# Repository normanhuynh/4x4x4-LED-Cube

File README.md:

# 4x4x4 LED Cube

This is a hand-soldered, reprogrammable 4x4x4 LED cube that uses Arduino - an open source IDE used to control user-made projects. This compact cube lights up with different patterns and is used to impress friends and family or as an amazing decoration for your desk. Of course, the hardware is not supplied in this repo - you will have to source that yourself.

# Main Components

  - ATmega328 microcontroller 
  - 2 x 74HC595N shift registers 
  - 4x4x4 cube matrix
  - 4 x BC327 transistors that control each layer of the cube.

Datasheets for the ATmega328 and for the 74HC595N are enclosed in the enclosed .zip file.

# How it Works - Quick Rundown
The LEDs are controlled by 2 shift registers that receive 16 bits from the programmed microcontroller. The shift registers then send out ON/OFF states to each layer of the cube’s cathodes before each corresponding layer anode is written to a LOW state in order to light the LEDs that were written to a LOW state. This process is rapidly repeated to give the impression that all LEDs in each layer are lit up simultaneously.

# Applications Used

  - **Arduino** - to create the LED cube sketch code
  - **Eagle** - to create the PCB and schematic

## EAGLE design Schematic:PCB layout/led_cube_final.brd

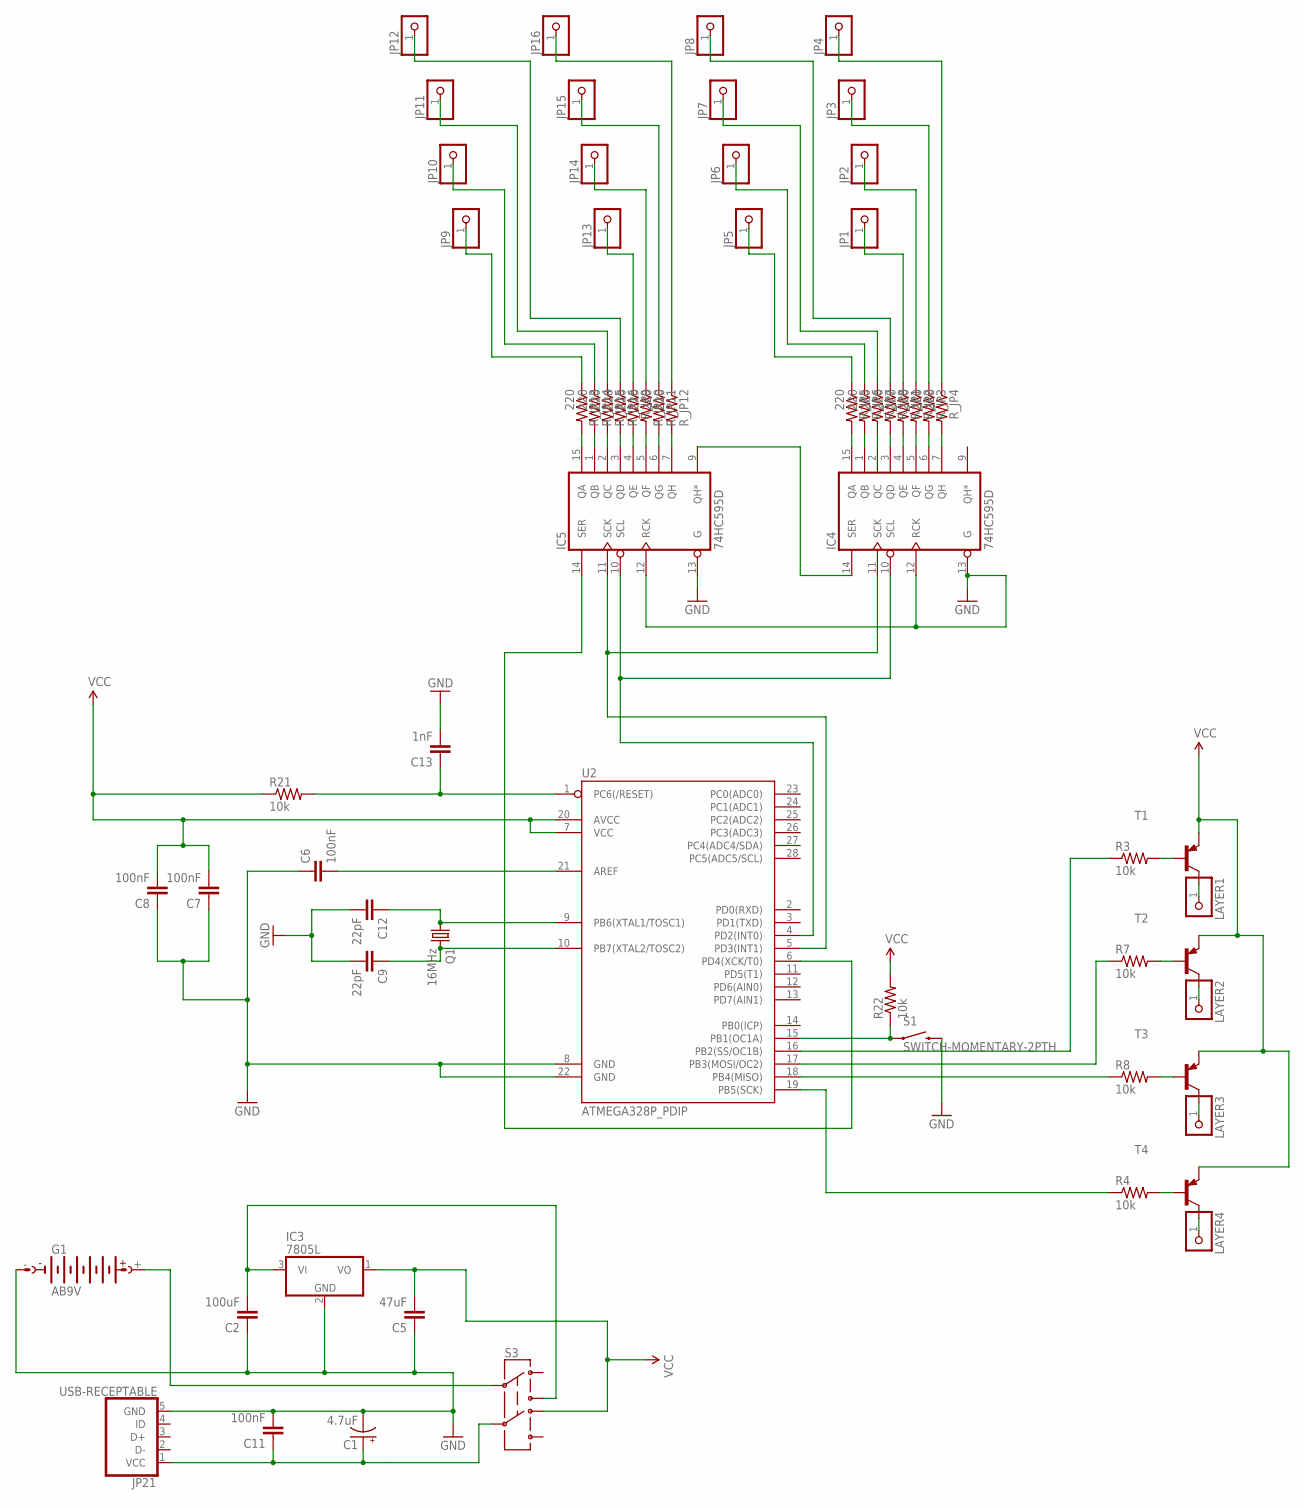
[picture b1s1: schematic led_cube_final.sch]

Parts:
C1: 4.7uF; E2-5
C2: 100uF; 0805
C5: 47uF; 0805
C6, C7, C8, C11: 100nF; 0805
C9, C12: 22pF; 0805
C13: 1nF; 0805
G1: AB9V
IC3: 7805L; TO92
IC4, IC5: 74HC595D; SO16
JP1, JP2, JP3, JP4, JP5, JP6, JP7, JP8, JP9, JP10, JP11, JP12, JP13, JP14, JP15, JP16: PINHD-1X1; 1X01
JP21: USB-RECEPTABLE; FCI-10103594-0001LF
LAYER1, LAYER2, LAYER3, LAYER4: PINHD-1X1; 1X01
Q1: 16MHz; HC49/S
R3, R4, R7, R8, R21, R22: 10k; 0805
R_JP1, R_JP2, R_JP3, R_JP4, R_JP5, R_JP6, R_JP7, R_JP8, R_JP9, R_JP10, R_JP11, R_JP12, R_JP13, R_JP14, R_JP15, R_JP16: 220; 0805
S1: SWITCH-MOMENTARY-2PTH; TACTILE-PTH
S3: SWITCH-DPDTOS; OS
T1, T2, T3, T4: BC327-16-PNP-TO92-EBC; TO92-EBC
U2: ATMEGA328P_PDIP; DIL28-3

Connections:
GND: C1.-, C2.1, C5.1, C6.1, C7.1, C8.1, C9.2, C11.2, C12.2, C13.2, G1.-, IC3.2 (GND), IC4.8 (GND), IC4.12 (RCK), IC4.13 (G), IC5.8 (GND), IC5.12 (RCK), IC5.13 (G), JP21.5 (GND), S1.3 (2), U2.8 (GND), U2.22 (GND)
unnamed: R4.2, T4.B
unnamed: R3.2, T1.B
unnamed: R7.2, T2.B
unnamed: IC4.10 (SCL), IC5.10 (SCL), U2.4 (PD2(INT0))
unnamed: JP1.1, R_JP1.1
unnamed: JP2.1, R_JP2.1
unnamed: R8.2, T3.B
unnamed: JP3.1, R_JP3.1
unnamed: JP4.1, R_JP4.1
unnamed: JP5.1, R_JP5.1
unnamed: JP6.1, R_JP6.1
unnamed: R22.1, S1.1, U2.15 (PB1(OC1A))
unnamed: LAYER3.1, T3.C
unnamed: R4.1, U2.19 (PB5(SCK))
unnamed: JP7.1, R_JP7.1
unnamed: JP8.1, R_JP8.1
unnamed: JP13.1, R_JP9.1
unnamed: JP14.1, R_JP10.1
unnamed: JP15.1, R_JP11.1
unnamed: JP16.1, R_JP12.1
unnamed: JP9.1, R_JP13.1
unnamed: JP10.1, R_JP14.1
unnamed: JP11.1, R_JP15.1
unnamed: JP12.1, R_JP16.1
unnamed: IC4.7 (QH), R_JP4.2
unnamed: IC4.6 (QG), R_JP3.2
unnamed: IC4.5 (QF), R_JP2.2
unnamed: IC4.4 (QE), R_JP1.2
unnamed: IC4.3 (QD), R_JP8.2
unnamed: IC4.2 (QC), R_JP7.2
unnamed: IC4.1 (QB), R_JP6.2
unnamed: IC4.15 (QA), R_JP5.2
unnamed: IC5.7 (QH), R_JP12.2
unnamed: IC5.6 (QG), R_JP11.2
unnamed: IC5.5 (QF), R_JP10.2
unnamed: IC5.4 (QE), R_JP9.2
unnamed: IC5.3 (QD), R_JP16.2
unnamed: IC5.2 (QC), R_JP15.2
unnamed: IC5.1 (QB), R_JP14.2
unnamed: IC5.15 (QA), R_JP13.2
unnamed: IC4.14 (SER), IC5.9 (QH*)
unnamed: LAYER4.1, T4.C
unnamed: R8.1, U2.18 (PB4(MISO))
unnamed: IC4.11 (SCK), IC5.11 (SCK), U2.5 (PD3(INT1))
unnamed: C2.2, IC3.3 (VI), S3.3
unnamed: C9.1, Q1.2, U2.10 (PB7(XTAL2/TOSC2))
unnamed: IC5.14 (SER), U2.6 (PD4(XCK/T0))
unnamed: R7.1, U2.17 (PB3(MOSI/OC2))
unnamed: C12.1, Q1.1, U2.9 (PB6(XTAL1/TOSC1))
unnamed: LAYER2.1, T2.C
unnamed: LAYER1.1, T1.C
unnamed: R3.1, U2.16 (PB2(SS/OC1B))
unnamed: C13.1, R21.2, U2.1 (PC6(/RESET))
unnamed: C6.2, U2.21 (AREF)
unnamed: G1.+, S3.2
unnamed: C1.+, C11.1, JP21.1 (VCC), S3.5
VCC: C5.2, C7.2, C8.2, IC3.1 (VO), IC4.16 (VCC), IC5.16 (VCC), R21.1, R22.2, S3.4, T1.E, T2.E, T3.E, T4.E, U2.7 (VCC), U2.20 (AVCC)

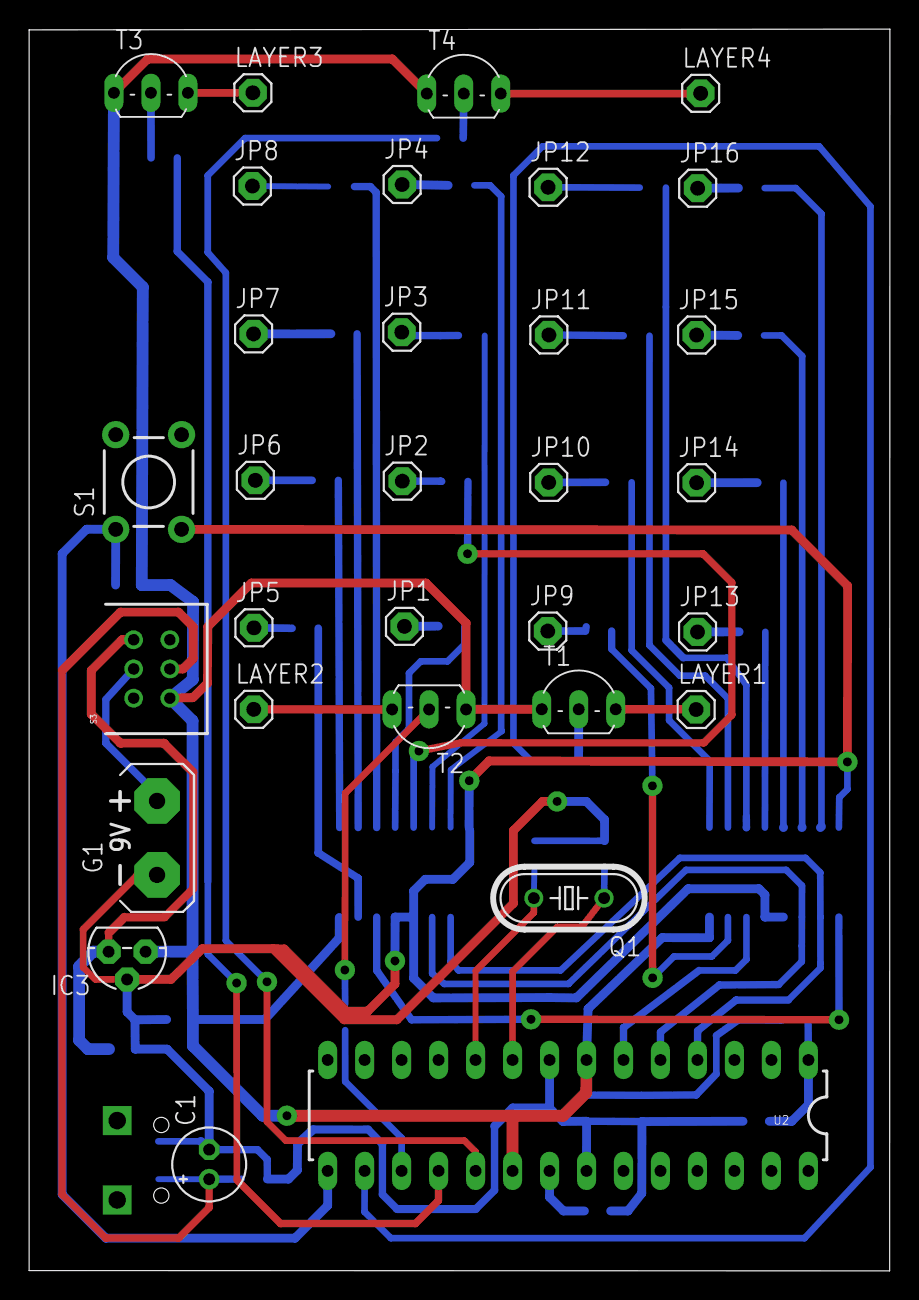
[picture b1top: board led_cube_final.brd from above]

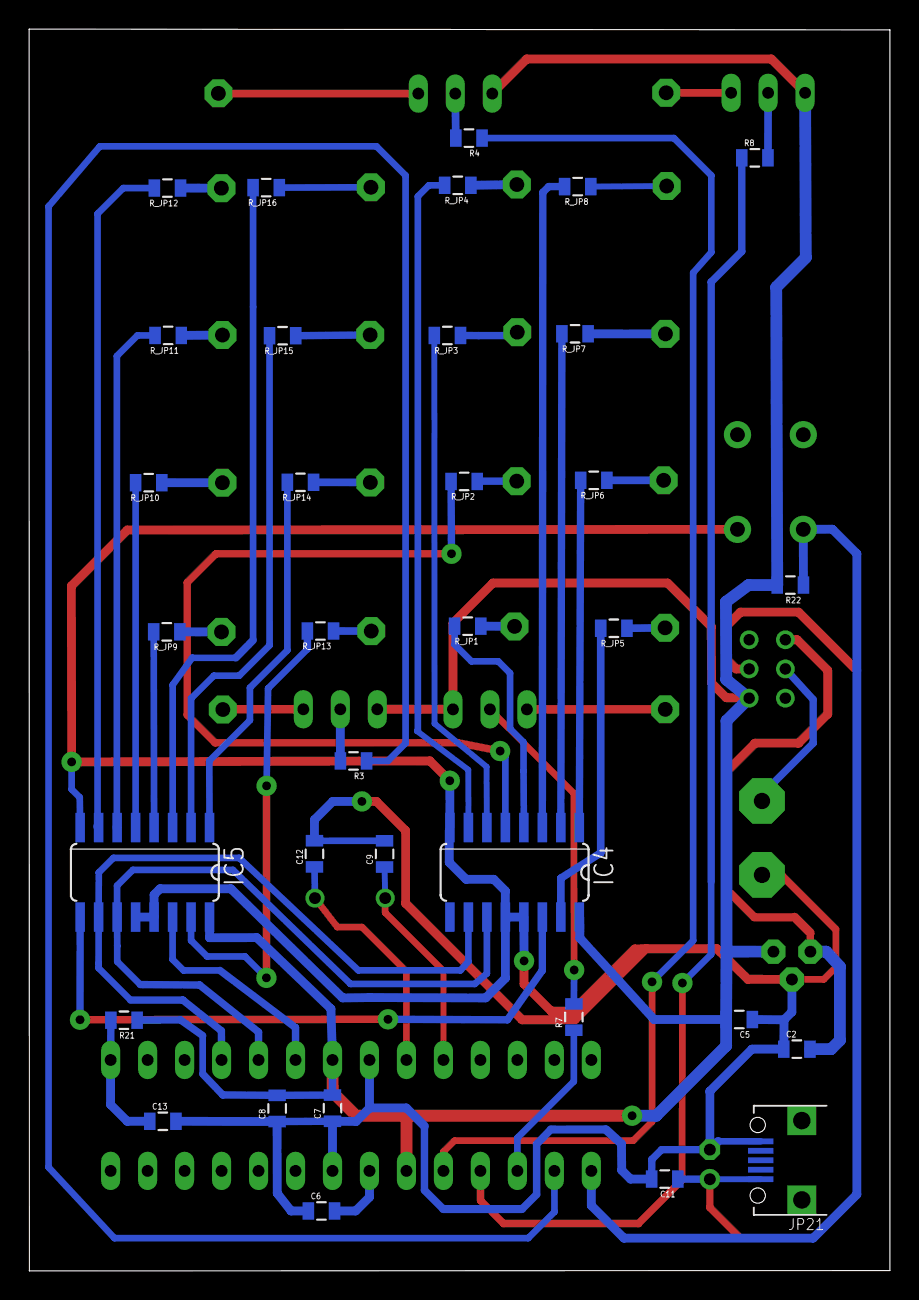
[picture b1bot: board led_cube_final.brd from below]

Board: 2 copper layers, 59.1 x 85.3 mm, 65 parts (34 on the bottom side), 58 nets.

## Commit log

2017-12-06 Added project files
2017-12-06 Update README with applications used

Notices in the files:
parts and their libraries:
SparkFun-Resistors: Licensing: Creative Commons ShareAlike 4.0 International - https://creativecommons.org/licenses/by-sa/4.0
